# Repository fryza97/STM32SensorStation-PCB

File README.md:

# STM32SensorStation-PCB

PCB to STM32SensorStation (https://github.com/fryza97/STM32SensorStation) project with STM32L010F4P6. The PCB has been designed for prototyping a weather station and as a devboard for other projects.

Image 1: Board project

Schematic 1: Power section

Schematic 2: Digital section

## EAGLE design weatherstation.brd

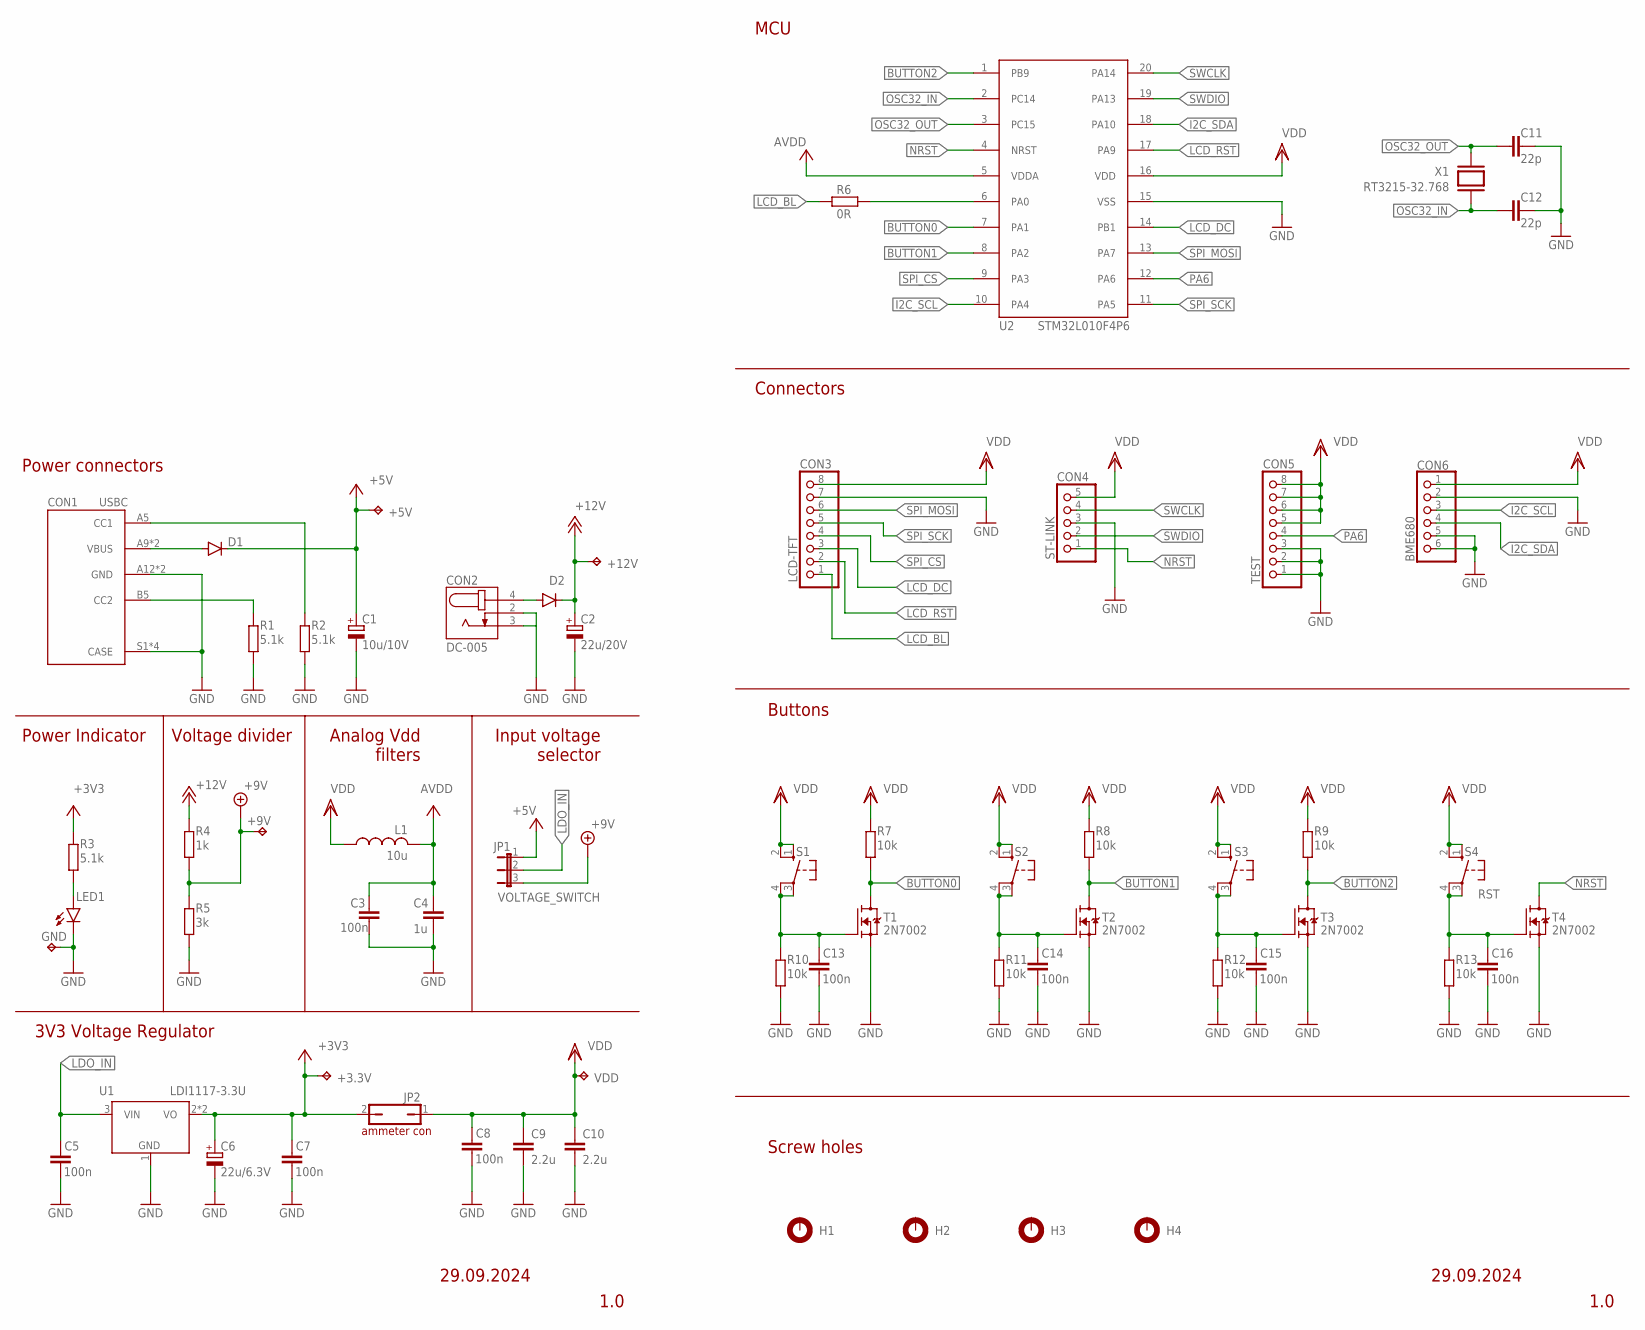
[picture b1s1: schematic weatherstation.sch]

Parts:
+3.3V, +5V, +9V, +12V: TPPAD1-13; P1-13
C1: 10u/10V; A/3216-18R
C2: 22u/20V; C/6032-28R
C3, C5, C7, C8, C13, C14, C15, C16: 100n; C0603K
C4: 1u; C0603K
C6: 22u/6.3V; A/3216-18R
C9, C10: 2.2u; C0805
C11, C12: 22p; C0603K
CON1: USBC; CUI_UJC-HP-3-SMT-TR
CON2: DC-005; NINIGI_DC-005
CON3: LCD-TFT; LCD
CON4: ST-LINK; 1X05
CON5: TEST; 1X08
CON6: BME680
D1: CGRM4001-G; SOD-123_MINI-SMA
D2: ES2D; SMB
GND: TPPAD1-13; P1-13
H1, H2, H3, H4: MOUNT-PAD-ROUND2.8; 2,8-PAD
JP1: VOLTAGE_SWITCH; JP2
JP2: JP1Q; JP1
L1: 10u; L2012C
LED1: LEDCHIPLED_1206; CHIPLED_1206
R1, R2, R3: 5.1k; R0805
R4: 1k; R0805
R5: 3k; R0805
R6: 0R; R0805
R7, R8, R9, R10, R11, R12, R13: 10k; R0805
S1: BUTTON0; B3F-10XX
S2: BUTTON1; B3F-10XX
S3: BUTTON2; B3F-10XX
S4: RST; B3F-10XX
T1, T2, T3, T4: 2N7002; SOT95P240X111-3N
U1: LDI1117-3.3U; SOT89
U2: STM32L010F4P6; TSSOP20
VDD: TPPAD1-13; P1-13
X1: RT3215-32.768; XTAL_RT3215-32.768-12.5-TR

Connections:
+3V3: +3.3V.TP, C6.+, C7.1, JP2.2, R3.2, U1.2 (VO), U1.2@1 (VO)
+5V: +5V.TP, C1.+, D1.C, JP1.1
+9V: +9V.TP, JP1.3, R4.2, R5.1
+12V: +12V.TP, C2.+, D2.C, R4.1
BUTTON0: R7.1, T1.3 (D), U2.7 (PA1)
BUTTON1: R8.1, T2.3 (D), U2.8 (PA2)
BUTTON2: R9.1, T3.3 (D), U2.1 (PB9)
GND: C1.-, C2.-, C3.1, C4.2, C5.2, C6.-, C7.2, C8.2, C9.2, C10.2, C11.1, C12.1, C13.2, C14.2, C15.2, C16.2, CON1.A12 (GND), CON1.B12 (GND), CON1.S1 (CASE), CON1.S2 (CASE), CON1.S3 (CASE), CON1.S4 (CASE), CON2.2 (4), CON2.3 (5), CON3.7 (GND), CON4.3, CON5.1, CON5.2, CON5.3, CON6.2 (GND), CON6.5 (SDO), CON6.6 (CS), GND.TP, LED1.C, R1.2, R2.1, R5.2, R10.1, R11.1, R12.1, R13.1, T1.2 (S), T2.2 (S), T3.2 (S), T4.2 (S), U1.1 (GND), U2.15 (VSS)
I2C_SCL: CON6.3 (SCL), U2.10 (PA4)
I2C_SDA: CON6.4 (SDA), U2.18 (PA10)
LCD_BL: CON3.1 (BL), R6.1
LCD_DC: CON3.3 (DC), U2.14 (PB1)
LCD_RST: CON3.2 (RST), U2.17 (PA9)
LDO_IN: C5.1, JP1.2, U1.3 (VIN)
unnamed: LED1.A, R3.1
unnamed: C16.1, R13.2, S4.3, S4.4 (P1), T4.1 (G)
unnamed: CON1.B5 (CC2), R1.1
unnamed: C13.1, R10.2, S1.3, S1.4 (P1), T1.1 (G)
unnamed: CON1.A5 (CC1), R2.2
unnamed: C14.1, R11.2, S2.3, S2.4 (P1), T2.1 (G)
unnamed: R6.2, U2.6 (PA0)
unnamed: C15.1, R12.2, S3.3, S3.4 (P1), T3.1 (G)
unnamed: CON1.A9 (VBUS), CON1.B9 (VBUS), D1.A
unnamed: CON2.4 (2), D2.A
NRST: CON4.1, T4.3 (D), U2.4 (NRST)
OSC32_IN: C12.2, U2.2 (PC14), X1.2
OSC32_OUT: C11.2, U2.3 (PC15), X1.1
PA6: CON5.4, U2.12 (PA6)
SPI_CS: CON3.4 (CS), U2.9 (PA3)
SPI_MOSI: CON3.6 (DIN), U2.13 (PA7)
SPI_SCK: CON3.5 (CLK), U2.11 (PA5)
SWCLK: CON4.4, U2.20 (PA14)
SWDIO: CON4.2, U2.19 (PA13)
VCC: C3.2, C4.1, L1.2, U2.5 (VDDA)
VDD: C8.1, C9.1, C10.1, CON3.8 (VCC), CON4.5, CON5.5, CON5.6, CON5.7, CON5.8, CON6.1 (VCC), JP2.1, L1.1, R7.2, R8.2, R9.2, S1.1 (S), S1.2 (S1), S2.1 (S), S2.2 (S1), S3.1 (S), S3.2 (S1), S4.1 (S), S4.2 (S1), U2.16 (VDD), VDD.TP

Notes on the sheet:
Power connectors
MCU
Buttons
ammeter con
1.0
Connectors
Power Indicator
Voltage divider
Analog Vdd filters
Input voltage selector
3V3 Voltage Regulator
Screw holes
29.09.2024

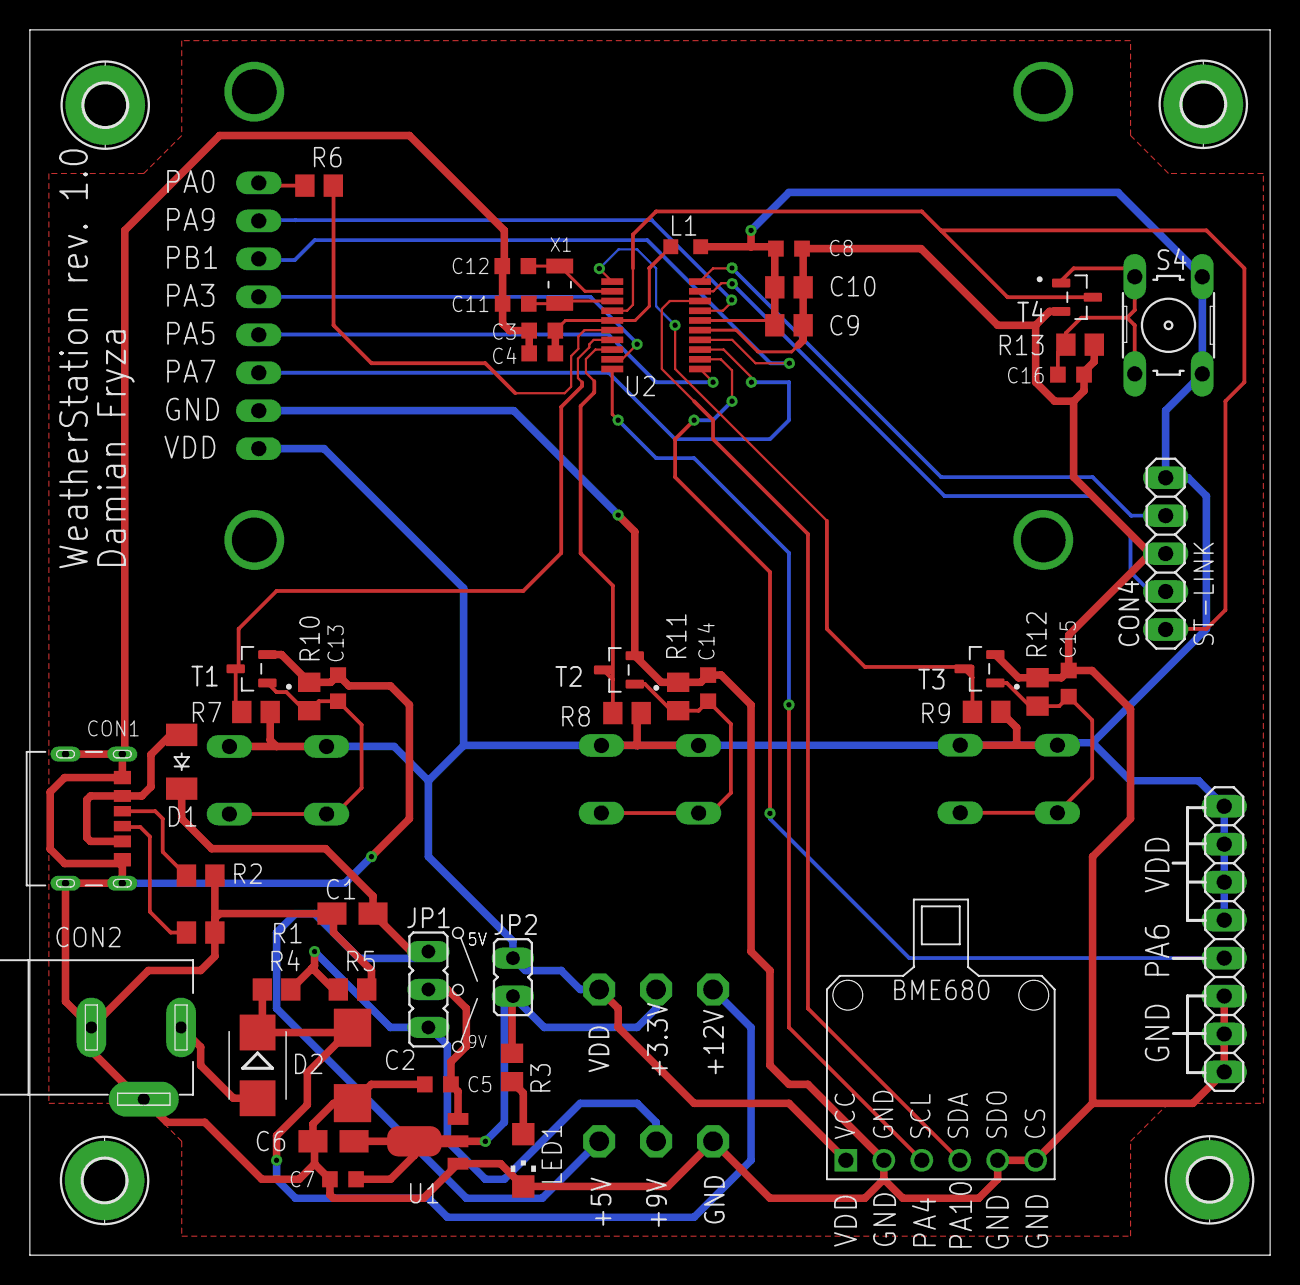
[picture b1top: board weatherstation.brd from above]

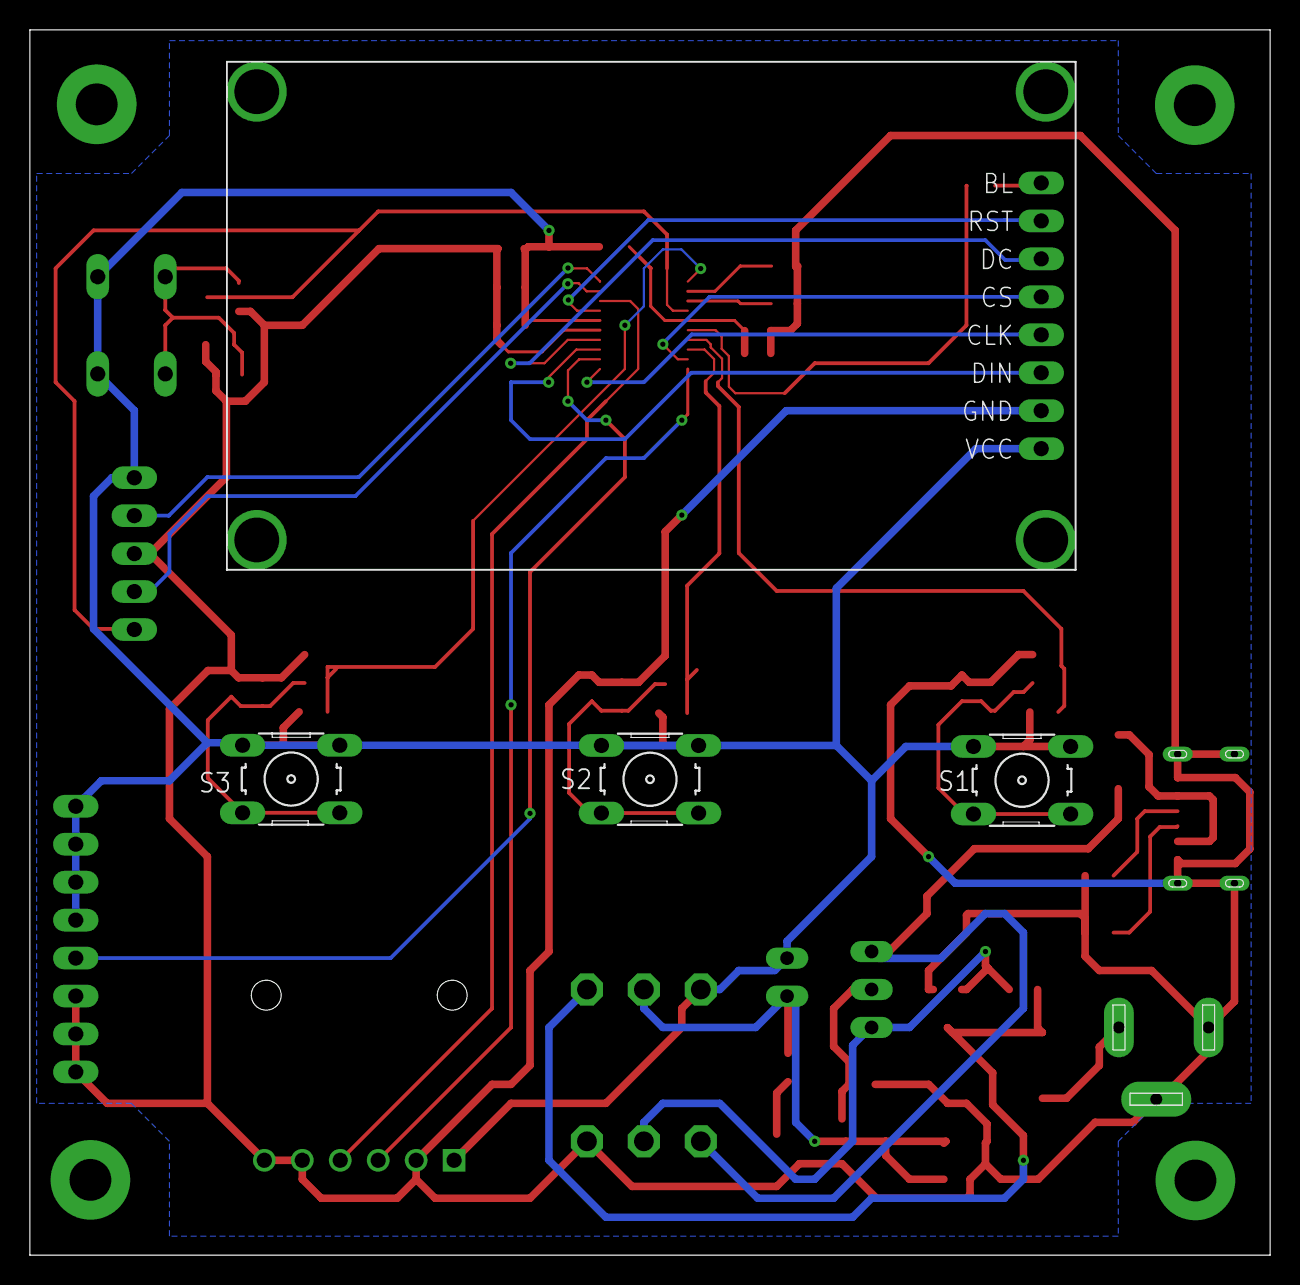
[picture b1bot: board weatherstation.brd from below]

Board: 2 copper layers, 83.0 x 82.0 mm, 62 parts (4 on the bottom side), 35 nets.

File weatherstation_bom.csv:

Part,Value,Package
C1,10u/10V,A/3216-18R
C2,22u/20V,C/6032-28R
C3,100n,C0603K
C4,1u,C0603K
C5,100n,C0603K
C6,22u/6.3V,A/3216-18R
C7,100n,C0603K
C8,100n,C0603K
C9,2.2u,C0805
C10,2.2u,C0805
C11,22p,C0603K
C12,22p,C0603K
C13,100n,C0603K
C14,100n,C0603K
C15,100n,C0603K
C16,100n,C0603K
CON1,USBC,CUI_UJC-HP-3-SMT-TR
CON2,DC-005,NINIGI_DC-005
CON3,LCD-TFT,goldpin 1X08
CON4,ST-LINK,goldpin 1X05
CON5,TEST,goldpin 1X08
CON6,BME680,goldpin 1X06
D1,Schottky,SMA
D2,Schottky,SMB
JP1,VOLTAGE_SWITCH,goldpin 1X03
JP2,AMMETER CON,goldpin 1X02
L1,10u,L2012C
LED1,,LED 1206
R1,5.1k,R0805
R2,5.1k,R0805
R3,5.1k,R0805
R4,1k,R0805
R5,3k,R0805
R6,0R,R0805
R7,10k,R0805
R8,10k,R0805
R9,10k,R0805
R10,10k,R0805
R11,10k,R0805
R12,10k,R0805
R13,10k,R0805
S1,BUTTON0,microswitch 4 pins
S2,BUTTON1,microswitch 4 pins
S3,BUTTON2,microswitch 4 pins
S4,RST,microswitch 4 pins
T1,2N7002,SOT95
T2,2N7002,SOT95
T3,2N7002,SOT95
T4,2N7002,SOT95
U1,LDI1117-3.3U,SOT89
U2,STM32L010F4P6,TSSOP20
X1,RT3215-32.768,XTAL_RT3215-32.768

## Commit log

2024-10-05 Add project to repository
2024-10-05 Changing wrong rev
2024-10-14 Update README.md
    Images update
2024-10-14 updated PCB descriptive layer
